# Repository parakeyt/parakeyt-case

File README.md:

# parakeyt-case
case generation for a parakeyt board

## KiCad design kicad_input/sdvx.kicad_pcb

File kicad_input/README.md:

# reference-design
the reference schematic and pcb, acting as an example of potential tool output.
firmware development and certain validation steps may be peformed on this board

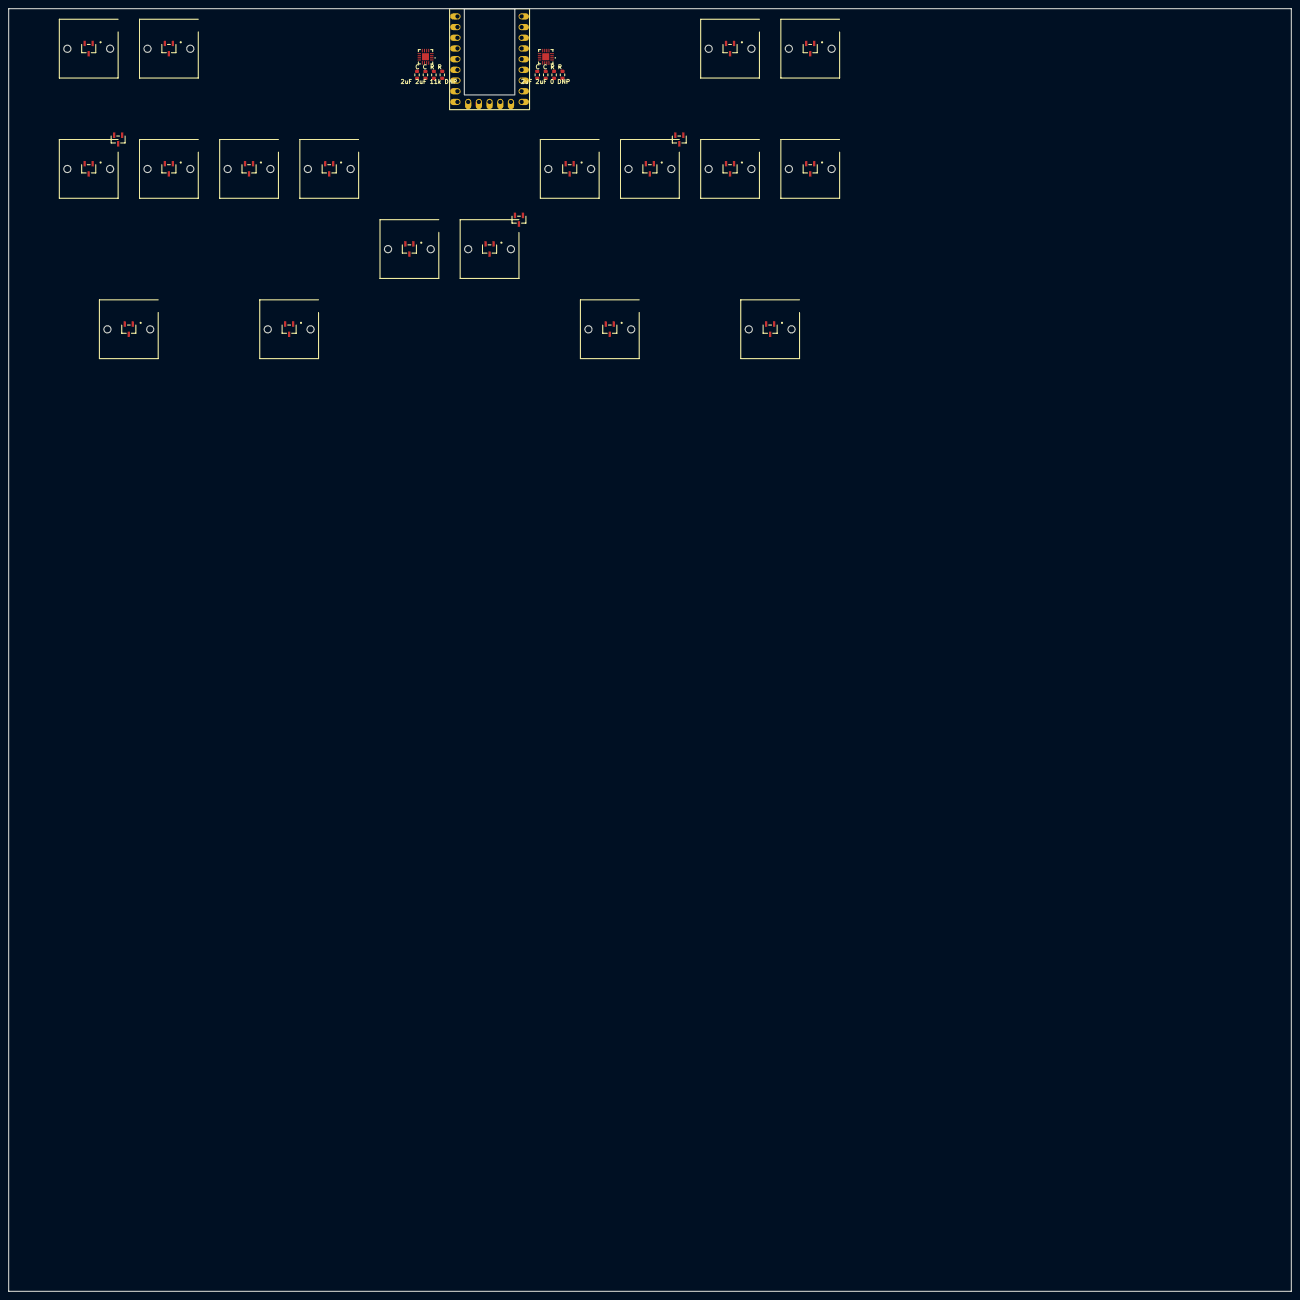
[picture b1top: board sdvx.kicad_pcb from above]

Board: 2 copper layers, 304.8 x 304.8 mm, 21 parts (0 on the bottom side), 21 nets, no tracks yet.

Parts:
R0: rp2040-zero-tht
R1, R9, R17: SC59_DIO_KeyswitchOutline_NoRuleArea_mosfet
R2, R3, R4, R5, R6, R7, R8, R10, R11, R12, R13, R14, R15, R16, R18: SC59_DIO_KeyswitchOutline_NoRuleArea_mosfet; SC59_DIO_KeyswitchOutline_NoRuleArea
R19, R20: WQFN16_RTE_TEX_with_caps_and_Rs

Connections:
+3.3v: R0.21, R1.6, R9.6, R17.6, R19.7, R19.10, R19.20, R20.7, R20.10
GND: R0.22, R1.3, R1.5, R2.3, R3.3, R4.3, R5.3, R6.3, R7.3, R8.3, R9.3, R9.5, R10.3, R11.3, R12.3, R13.3, R14.3, R15.3, R16.3, R17.3, R17.5, R18.3, R19.9, R19.17, R19.19, R19.23, R20.9, R20.17, R20.18, R20.19, R20.20, R20.21, R20.22, R20.23
SCL: R0.2, R19.13, R20.13
SDA: R0.1, R19.14, R20.14
addr10: R19.11, R19.21, R19.24
addr20: R20.11, R20.24
decap10: R19.8, R19.18, R19.22
m0c0: R1.2, R9.2, R17.2, R19.15
m0c1: R2.2, R10.2, R18.2, R19.16
m0c2: R3.2, R11.2, R19.1
m0c3: R4.2, R12.2, R19.2
m0c4: R5.2, R13.2, R19.3
m0c5: R6.2, R14.2, R19.4
m0c6: R7.2, R15.2, R19.5
m0c7: R8.2, R16.2, R19.6
m0r0: R1.4, R20.15
m0r0MOS: R1.1, R2.1, R3.1, R4.1, R5.1, R6.1, R7.1, R8.1
m0r1: R9.4, R20.16
m0r1MOS: R9.1, R10.1, R11.1, R12.1, R13.1, R14.1, R15.1, R16.1
m0r2: R17.4, R20.1
m0r2MOS: R17.1, R18.1

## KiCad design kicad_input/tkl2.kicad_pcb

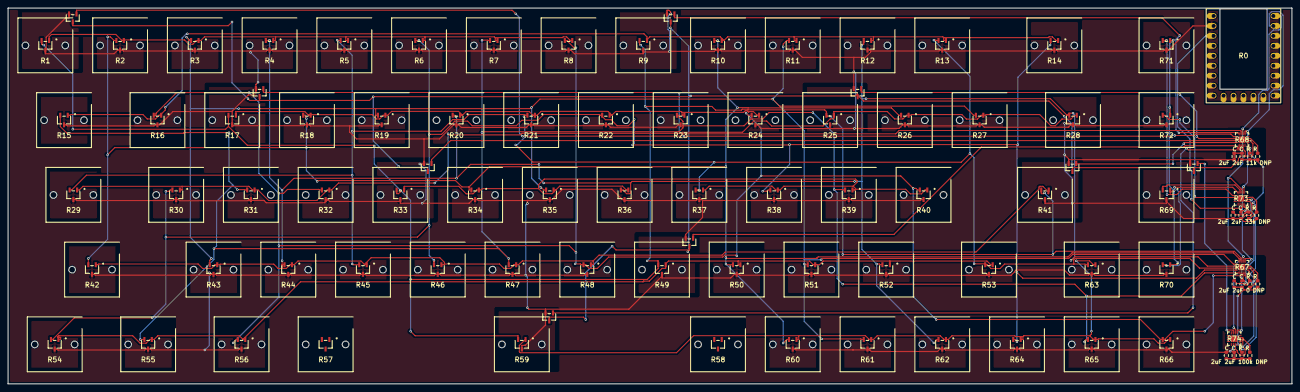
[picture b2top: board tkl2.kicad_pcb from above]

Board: 2 copper layers, 327.2 x 95.8 mm, 75 parts (0 on the bottom side), 40 nets.

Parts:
R0: rp2040-zero-tht
R1, R9, R17, R25, R33, R41, R49, R59, R69: SC59_DIO_KeyswitchOutline_NoRuleArea_mosfet
R2, R3, R4, R5, R6, R7, R8, R10, R11, R12, R13, R14, R15, R16, R18, R19, R20, R21, R22, R23, R24, R26, R27, R28, R29, R30, R31, R32, R34, R35, R36, R37, R38, R39, R40, R42, R43, R44, R45, R46, R47, R48, R50, R51, R52, R53, R54, R55, R56, R57, R58, R60, R61, R62, R63, R64, R65, R66, R70, R71, R72: SC59_DIO_KeyswitchOutline_NoRuleArea_mosfet; SC59_DIO_KeyswitchOutline_NoRuleArea
R67, R68, R73, R74: WQFN16_RTE_TEX_with_caps_and_Rs

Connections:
+3.3v: R0.21, R1.6, R9.6, R17.6, R25.6, R33.6, R41.6, R49.6, R59.6, R67.7, R67.10, R67.20, R68.7, R68.10, R69.6, R73.7, R73.10, R73.20, R74.7, R74.10
GND: R0.22, R1.3, R1.5, R2.3, R3.3, R4.3, R5.3, R6.3, R7.3, R8.3, R9.3, R9.5, R10.3, R11.3, R12.3, R13.3, R14.3, R15.3, R16.3, R17.3, R17.5, R18.3, R19.3, R20.3, R21.3, R22.3, R23.3, R24.3, R25.3, R25.5, R26.3, R27.3, R28.3, R29.3, R30.3, R31.3, R32.3, R33.3, R33.5, R34.3, R35.3, R36.3, R37.3, R38.3, R39.3, R40.3, R41.3, R41.5, R42.3, R43.3, R44.3, R45.3, R46.3, R47.3, R48.3, R49.3, R49.5, R50.3, R51.3, R52.3, R53.3, R54.3, R55.3, R56.3, R59.3, R59.5, R60.3, R61.3, R62.3, R63.3, R64.3, R65.3, R66.3, R67.9, R67.17, R67.19, R67.23, R68.9, R68.17, R68.18, R68.19, R68.20, R68.21, R68.22, R68.23, R69.3, R69.5, R70.3, R71.3, R72.3, R73.9, R73.17, R73.19, R73.23, R74.9, R74.17, R74.18, R74.19, R74.20, R74.21, R74.22, R74.23
SCL: R0.2, R67.13, R68.13, R73.13, R74.13
SDA: R0.1, R67.14, R68.14, R73.14, R74.14
addr10: R67.11, R67.21, R67.24
addr11: R73.11, R73.21, R73.24
addr20: R68.11, R68.24
addr21: R74.11, R74.24
decap10: R67.8, R67.18, R67.22
decap11: R73.8, R73.18, R73.22
m0c0: R1.2, R9.2, R17.2, R25.2, R33.2, R41.2, R49.2, R59.2, R67.15
m0c1: R2.2, R10.2, R18.2, R26.2, R34.2, R42.2, R50.2, R60.2, R67.16
m0c2: R3.2, R11.2, R19.2, R27.2, R35.2, R43.2, R51.2, R61.2, R67.1
m0c3: R4.2, R12.2, R20.2, R28.2, R36.2, R44.2, R52.2, R62.2, R67.2
m0c4: R5.2, R13.2, R21.2, R29.2, R37.2, R45.2, R53.2, R63.2, R67.3
m0c5: R6.2, R14.2, R22.2, R30.2, R38.2, R46.2, R54.2, R64.2, R67.4
m0c6: R7.2, R15.2, R23.2, R31.2, R39.2, R47.2, R55.2, R65.2, R67.5
m0c7: R8.2, R16.2, R24.2, R32.2, R40.2, R48.2, R56.2, R66.2, R67.6
m0r0: R1.4, R68.15
m0r0MOS: R1.1, R2.1, R3.1, R4.1, R5.1, R6.1, R7.1, R8.1
m0r1: R9.4, R68.16
m0r1MOS: R9.1, R10.1, R11.1, R12.1, R13.1, R14.1, R15.1, R16.1
m0r2: R17.4, R68.1
m0r2MOS: R17.1, R18.1, R19.1, R20.1, R21.1, R22.1, R23.1, R24.1
m0r3: R25.4, R68.2
m0r3MOS: R25.1, R26.1, R27.1, R28.1, R29.1, R30.1, R31.1, R32.1
m0r4: R33.4, R68.3
m0r4MOS: R33.1, R34.1, R35.1, R36.1, R37.1, R38.1, R39.1, R40.1
m0r5: R41.4, R68.4
m0r5MOS: R41.1, R42.1, R43.1, R44.1, R45.1, R46.1, R47.1, R48.1
m0r6: R49.4, R68.5
m0r6MOS: R49.1, R50.1, R51.1, R52.1, R53.1, R54.1, R55.1, R56.1
m0r7: R59.4, R68.6
m0r7MOS: R59.1, R60.1, R61.1, R62.1, R63.1, R64.1, R65.1, R66.1
m1c0: R69.2, R73.15
m1c1: R70.2, R73.16
m1c2: R71.2, R73.1
m1c3: R72.2, R73.2
m1r0: R69.4, R74.15
m1r0MOS: R69.1, R70.1, R71.1, R72.1

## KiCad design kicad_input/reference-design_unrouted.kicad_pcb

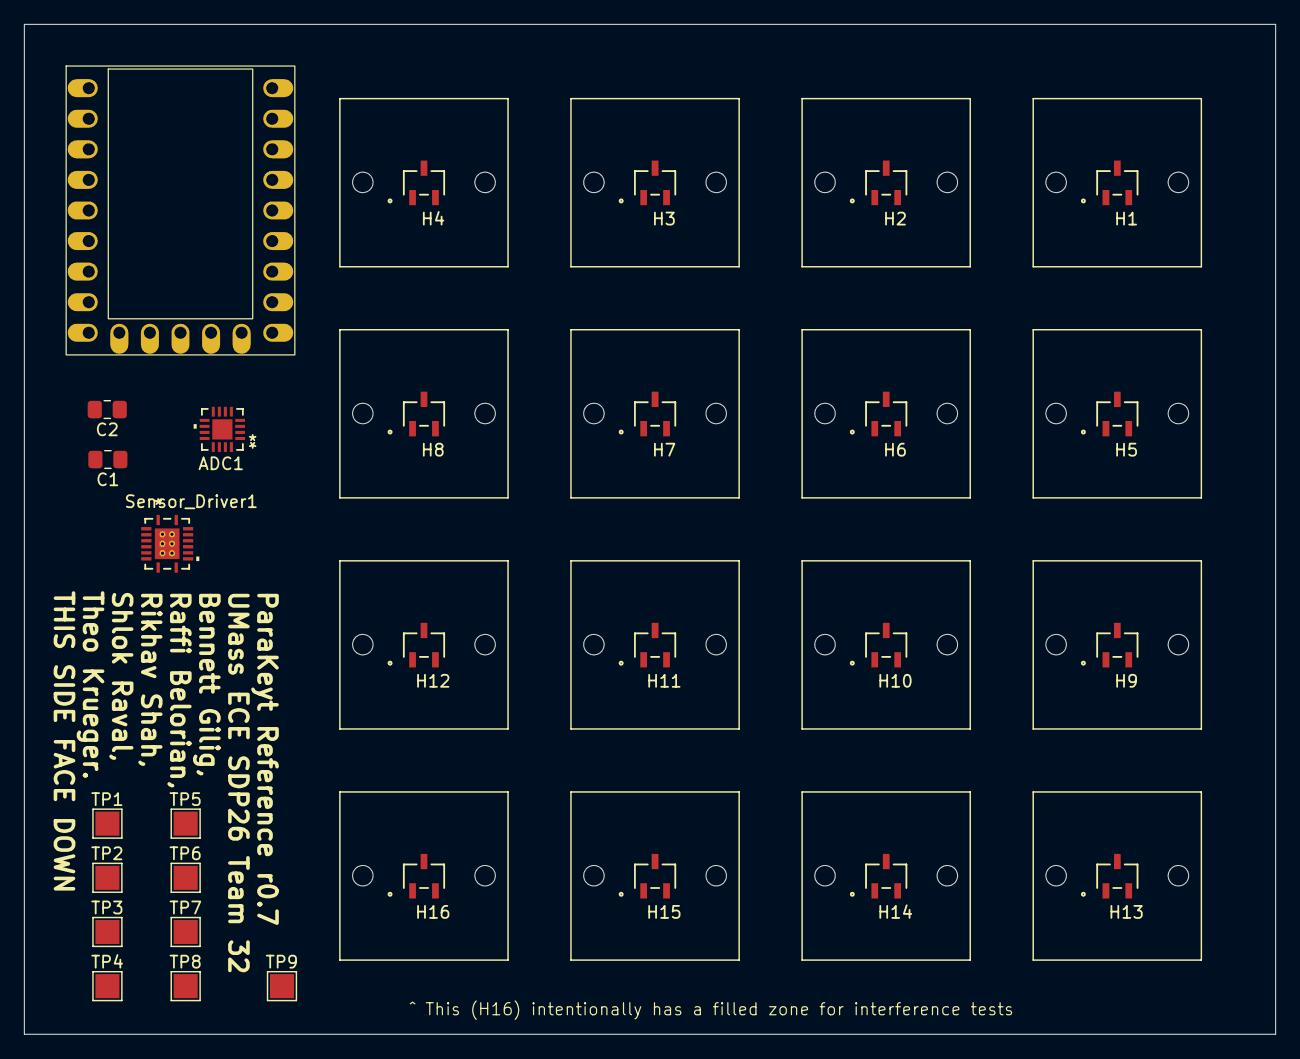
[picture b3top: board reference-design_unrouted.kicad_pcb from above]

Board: 2 copper layers, 104.0 x 83.9 mm, 30 parts (0 on the bottom side), 13 nets, no tracks yet.

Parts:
ADC1: TLA2528IRTER; WQFN16_RTE_TEX
C1, C2: 2uF; C_0805_2012Metric_Pad1.18x1.45mm_HandSolder
H1, H2, H3, H4, H5, H6, H7, H8, H9, H10, H11, H12, H13, H14, H15, H16: AH49FNTR-G1; SC59_DIO_KeyswitchOutline_NoRuleArea
MCU1: RP2040-Zero; rp2040-zero-tht
Sensor_Driver1: TLC59108IRGYR; RGY16_2P55X2P05
TP1: col0; TestPoint_Pad_2.0x2.0mm
TP2: col1; TestPoint_Pad_2.0x2.0mm
TP3: col2; TestPoint_Pad_2.0x2.0mm
TP4: col3; TestPoint_Pad_2.0x2.0mm
TP5: row0; TestPoint_Pad_2.0x2.0mm
TP6: row1; TestPoint_Pad_2.0x2.0mm
TP7: row2; TestPoint_Pad_2.0x2.0mm
TP8: row3; TestPoint_Pad_2.0x2.0mm
TP9: GND; TestPoint_Pad_2.0x2.0mm

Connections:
+3.3V: ADC1.7 (AVDD), ADC1.10 (DVDD), C1.1, MCU1.21 (3V3), Sensor_Driver1.13 (*RESET), Sensor_Driver1.16 (VCC)
GND: ADC1.9 (GND), ADC1.11 (ADDR), ADC1.17 (GND), C1.2, C2.2, H1.3 (GND), H2.3 (GND), H3.3 (GND), H4.3 (GND), H5.3 (GND), H6.3 (GND), H7.3 (GND), H8.3 (GND), H9.3 (GND), H10.3 (GND), H11.3 (GND), H12.3 (GND), H13.3 (GND), H14.3 (GND), H15.3 (GND), H16.3 (GND), MCU1.22 (GND), Sensor_Driver1.1 (A0), Sensor_Driver1.2 (A1), Sensor_Driver1.3 (A2), Sensor_Driver1.8 (GND), Sensor_Driver1.17 (EPAD), Sensor_Driver1.18 (TV0), Sensor_Driver1.19 (TV1), Sensor_Driver1.20 (TV2), Sensor_Driver1.21 (TV3), Sensor_Driver1.22 (TV4), Sensor_Driver1.23 (TV5), TP9.1
unnamed: ADC1.8 (DECAP), C2.1
col0: ADC1.15 (AIN0/GPIO0), H1.2 (OUT), H5.2 (OUT), H9.2 (OUT), H13.2 (OUT), TP1.1
col1: ADC1.16 (AIN1/GPIO1), H2.2 (OUT), H6.2 (OUT), H10.2 (OUT), H14.2 (OUT), TP2.1
col2: ADC1.1 (AIN2/GPIO2), H3.2 (OUT), H7.2 (OUT), H11.2 (OUT), H15.2 (OUT), TP3.1
col3: ADC1.2 (AIN3/GPIO3), H4.2 (OUT), H8.2 (OUT), H12.2 (OUT), H16.2 (OUT), TP4.1
i2c0_scl: ADC1.13 (SCL), MCU1.2 (1), Sensor_Driver1.14 (SCL)
i2c0_sda: ADC1.14 (SDA), MCU1.1 (0), Sensor_Driver1.15 (SDA)
row0: H1.1 (VCC), H2.1 (VCC), H3.1 (VCC), H4.1 (VCC), Sensor_Driver1.12 (*OUT7), TP5.1
row1: H5.1 (VCC), H6.1 (VCC), H7.1 (VCC), H8.1 (VCC), Sensor_Driver1.11 (*OUT6), TP6.1
row2: H9.1 (VCC), H10.1 (VCC), H11.1 (VCC), H12.1 (VCC), Sensor_Driver1.10 (*OUT5), TP7.1
row3: H13.1 (VCC), H14.1 (VCC), H15.1 (VCC), H16.1 (VCC), Sensor_Driver1.9 (*OUT4), TP8.1

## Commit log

2026-03-11 Working parcing and CADQuery pipeline for reference schematic
2026-03-19 new input design
2026-03-19 new reference output
2026-04-29 good working case generation
2026-04-29 yay all keyboard cases work
2026-04-30 fixed all issues, works great yay
2026-05-01 final minor change
2026-05-01 fixed parse_kicad.py
